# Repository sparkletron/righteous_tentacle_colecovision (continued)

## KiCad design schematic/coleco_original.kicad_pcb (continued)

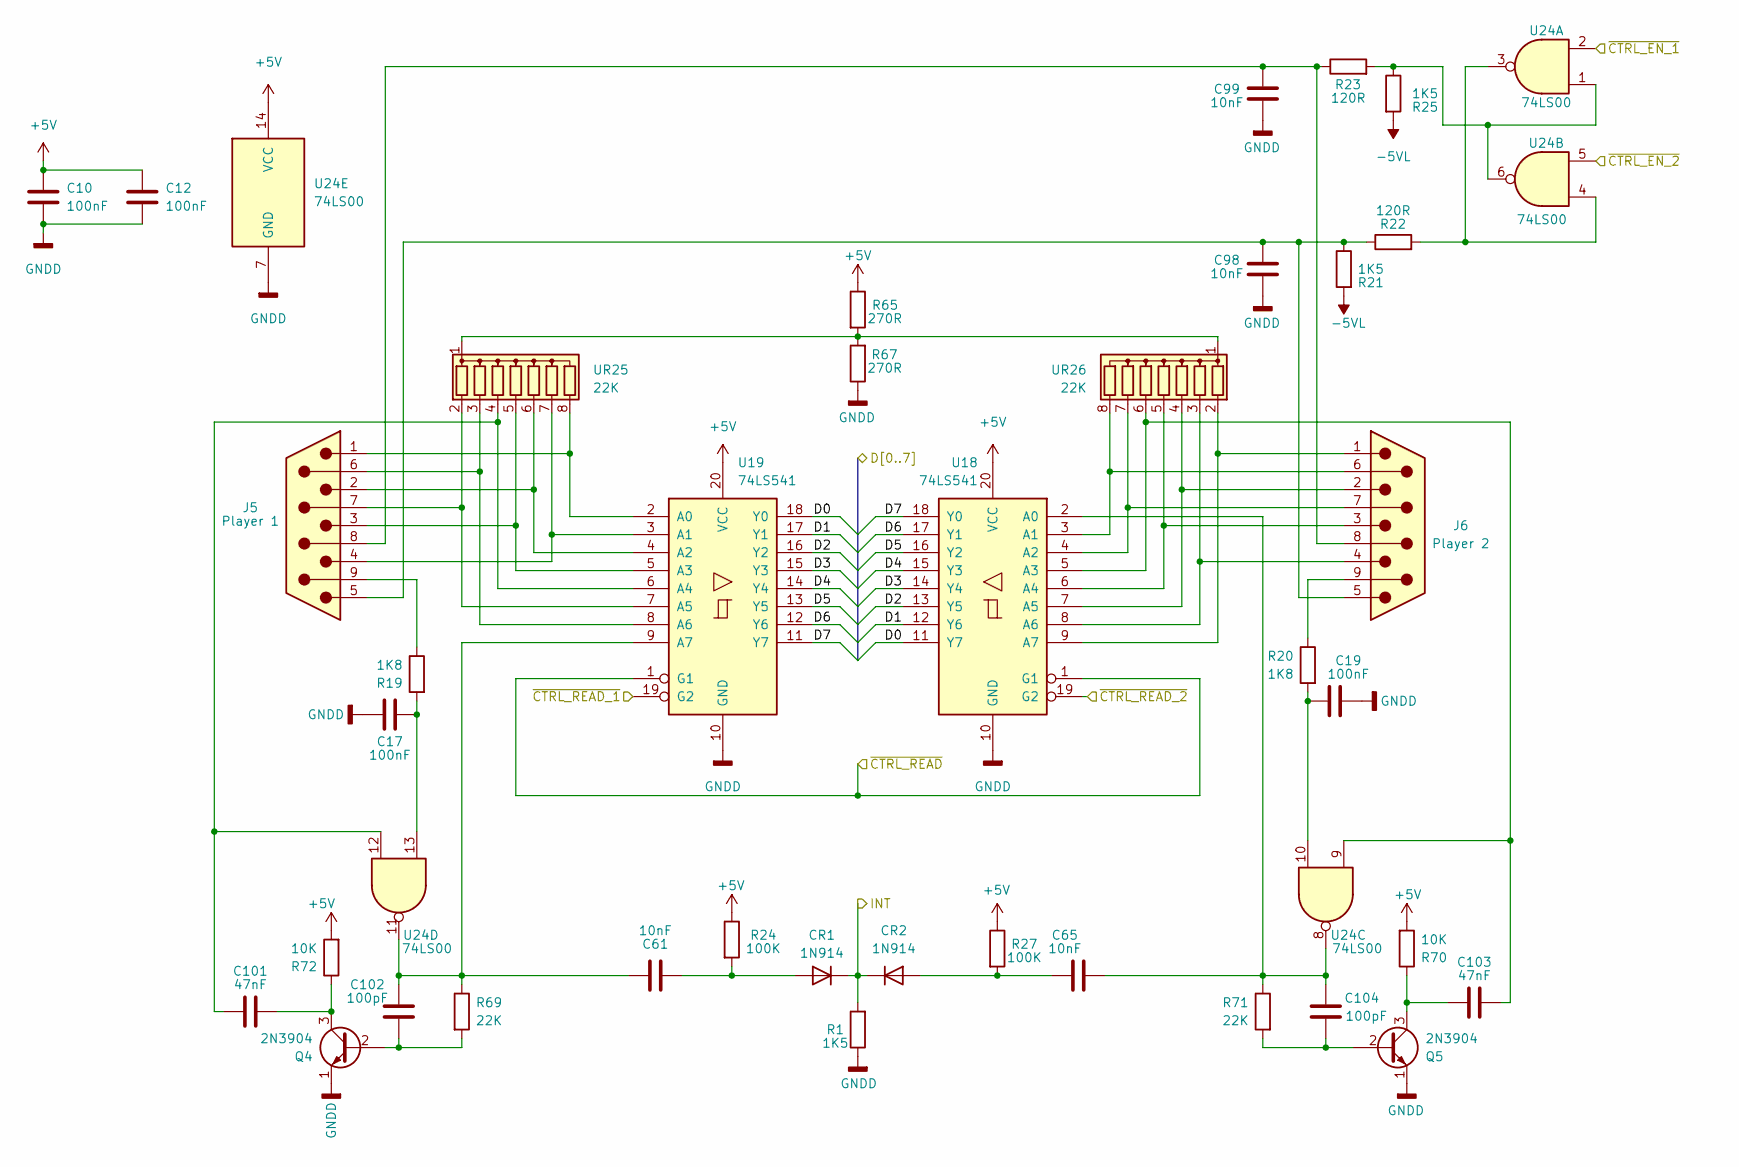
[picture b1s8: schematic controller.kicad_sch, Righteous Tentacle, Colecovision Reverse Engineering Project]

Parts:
C10, C12, C17, C19: 100nF; C_Disc_D7.0mm_W2.5mm_P5.00mm
C61, C65, C98, C99: 10nF; C_Disc_D7.0mm_W2.5mm_P5.00mm
C101, C103: 47nF; C_Disc_D7.0mm_W2.5mm_P5.00mm
C102, C104: 100pF; C_Disc_D7.0mm_W2.5mm_P5.00mm
CR1, CR2: 1N914; D_DO-35_SOD27_P10.16mm_Horizontal
J5: Player 1; DSUB-9_Male_Horizontal_P2.77x2.84mm_EdgePinOffset7.70mm_Hou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
J6: Player 2; DSUB-9_Male_Horizontal_P2.77x2.84mm_EdgePinOffset7.70mm_Hou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
Q4, Q5: 2N3904; TO-92_Wide
R1, R21, R25: 1K5; R_Axial_DIN0207_L6.3mm_D2.5mm_P10.16mm_Horizontal
R19, R20: 1K8; R_Axial_DIN0207_L6.3mm_D2.5mm_P10.16mm_Horizontal
R22, R23: 120R; R_Axial_DIN0207_L6.3mm_D2.5mm_P10.16mm_Horizontal
R24, R27: 100K; R_Axial_DIN0207_L6.3mm_D2.5mm_P10.16mm_Horizontal
R65, R67: 270R; R_Axial_DIN0207_L6.3mm_D2.5mm_P10.16mm_Horizontal
R69, R71: 22K; R_Axial_DIN0207_L6.3mm_D2.5mm_P10.16mm_Horizontal
R70, R72: 10K; R_Axial_DIN0207_L6.3mm_D2.5mm_P10.16mm_Horizontal
U18, U19: 74LS541; DIP-20_W7.62mm_LongPads
U24: 74LS00; DIP-14_W7.62mm_LongPads
UR25, UR26: 22K; R_Array_SIP8

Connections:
+5V: C10.1, C12.1, R24.1, R27.1, R65.1, R70.2, R72.2, U18.20 (VCC), U19.20 (VCC), U24.14 (VCC); also elsewhere on the board
-5VL: R21.2, R25.2; also elsewhere on the board
/clock_reset_misc_logic/INT: CR1.1 (K), CR2.1 (K), R1.2; also elsewhere on the board
/clock_reset_misc_logic/~CTRL_READ_2: U18.19 (G2); also elsewhere on the board
/controller/~CTRL_EN_1: U24.2; also elsewhere on the board
/controller/~CTRL_EN_2: U24.5; also elsewhere on the board
/controller/~CTRL_READ: U18.1 (G1), U19.1 (G1); also elsewhere on the board
/cpu/A1: U19.19 (G2); also elsewhere on the board
/cpu/D0: U18.11 (Y7), U19.18 (Y0); also elsewhere on the board
/cpu/D1: U18.12 (Y6), U19.17 (Y1); also elsewhere on the board
/cpu/D2: U18.13 (Y5), U19.16 (Y2); also elsewhere on the board
/cpu/D3: U18.14 (Y4), U19.15 (Y3); also elsewhere on the board
/cpu/D4: U18.15 (Y3), U19.14 (Y4); also elsewhere on the board
/cpu/D5: U18.16 (Y2), U19.13 (Y5); also elsewhere on the board
/cpu/D6: U18.17 (Y1), U19.12 (Y6); also elsewhere on the board
/cpu/D7: U18.18 (Y0), U19.11 (Y7); also elsewhere on the board
GNDD: C10.2, C12.2, C17.1, C19.1, C98.1, C99.2, Q4.1 (E), Q5.1 (E), R1.1, R67.1, U18.10 (GND), U19.10 (GND), U24.7 (GND); also elsewhere on the board
unnamed: C17.2, R19.2, U24.13
unnamed: C19.2, R20.2, U24.10
unnamed: C61.1, CR1.2 (A), R24.2
unnamed: C65.1, CR2.2 (A), R27.2
unnamed: C98.2, J5.5, J6.5, R21.1, R22.1
unnamed: C99.1, J5.8, J6.8, R23.1
unnamed: C101.1, Q4.3 (C), R72.1
unnamed: C101.2, U19.6 (A4), U24.12, UR25.4 (R3)
unnamed: C102.1, Q4.2 (B), R69.2
unnamed: C61.2, C102.2, R69.1, U19.9 (A7), U24.11
unnamed: C103.1, Q5.3 (C), R70.1
unnamed: C103.2, U18.5 (A3), U24.9, UR26.6 (R5)
unnamed: C104.1, Q5.2 (B), R71.2
unnamed: C65.2, C104.2, R71.1, U18.2 (A0), U24.8
unnamed: J5.1, U19.2 (A0), UR25.8 (R7)
unnamed: J5.2, U19.4 (A2), UR25.6 (R5)
unnamed: J5.3, U19.5 (A3), UR25.5 (R4)
unnamed: J5.4, U19.3 (A1), UR25.7 (R6)
unnamed: J5.6, U19.8 (A6), UR25.3 (R2)
unnamed: J5.7, U19.7 (A5), UR25.2 (R1)
unnamed: J5.9, R19.1
unnamed: J6.1, U18.9 (A7), UR26.2 (R1)
unnamed: J6.2, U18.7 (A5), UR26.4 (R3)
unnamed: J6.3, U18.6 (A4), UR26.5 (R4)
unnamed: J6.4, U18.8 (A6), UR26.3 (R2)
unnamed: J6.6, U18.3 (A1), UR26.8 (R7)
unnamed: J6.7, U18.4 (A2), UR26.7 (R6)
unnamed: J6.9, R20.1
unnamed: R22.2, U24.3, U24.4
unnamed: R23.2, R25.1, U24.1, U24.6
unnamed: R65.2, R67.2, UR25.1 (common), UR26.1 (common)

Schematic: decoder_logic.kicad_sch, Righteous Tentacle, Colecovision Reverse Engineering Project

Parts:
C2: 100nF; C_Disc_D7.0mm_W2.5mm_P5.00mm
U5, U6: 74LS138; DIP-16_W7.62mm_LongPads

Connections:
+5V: C2.1, U5.16 (VCC); also elsewhere on the board
+5VD: U6.16 (VCC); also elsewhere on the board
/clock_reset_misc_logic/RFSH: U5.5 (E2); also elsewhere on the board
/clock_reset_misc_logic/~AUD_DECODE_2: U6.5 (E2); also elsewhere on the board
/controller/~CTRL_EN_1: U6.11 (O4); also elsewhere on the board
/controller/~CTRL_EN_2: U6.15 (O0); also elsewhere on the board
/controller/~CTRL_READ: U6.7 (O7); also elsewhere on the board
/cpu/A5: U6.2 (A1); also elsewhere on the board
/cpu/A6: U6.3 (A2); also elsewhere on the board
/cpu/A7: U6.6 (E3); also elsewhere on the board
/cpu/A13: U5.1 (A0); also elsewhere on the board
/cpu/A14: U5.2 (A1); also elsewhere on the board
/cpu/A15: U5.3 (A2); also elsewhere on the board
/cpu/~IORQ: U6.4 (E1); also elsewhere on the board
/cpu/~MREQ: U5.4 (E1); also elsewhere on the board
/cpu/~WR: U6.1 (A0); also elsewhere on the board
/decoder_logic/AUX_DECODE_1: U5.6 (E3); also elsewhere on the board
/decoder_logic/~CSR: U6.12 (O3); also elsewhere on the board
/decoder_logic/~CSW: U6.13 (O2); also elsewhere on the board
/decoder_logic/~CS_h2000: U5.14 (O1); also elsewhere on the board
/decoder_logic/~CS_h4000: U5.13 (O2); also elsewhere on the board
/decoder_logic/~CS_h8000: U5.11 (O4); also elsewhere on the board
/decoder_logic/~CS_hA000: U5.10 (O5); also elsewhere on the board
/decoder_logic/~CS_hC000: U5.9 (O6); also elsewhere on the board
/decoder_logic/~CS_hE000: U5.7 (O7); also elsewhere on the board
/decoder_logic/~RAM_CS: U5.12 (O3); also elsewhere on the board
/decoder_logic/~ROM_ENABLE: U5.15 (O0); also elsewhere on the board
/decoder_logic/~SND_ENABLE: U6.9 (O6); also elsewhere on the board
GNDD: C2.2, U5.8 (GND), U6.8 (GND); also elsewhere on the board

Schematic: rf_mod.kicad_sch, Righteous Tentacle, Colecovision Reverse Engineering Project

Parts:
C57, C78: 10nF; C_Disc_D7.0mm_W2.5mm_P5.00mm
C60, C69: 47nF; C_Disc_D7.0mm_W2.5mm_P5.00mm
C62, C63: 470pF; C_Disc_D7.0mm_W2.5mm_P5.00mm
C64: 120pF; C_Disc_D7.0mm_W2.5mm_P5.00mm
C66, C67, C88, C100: 100nF; C_Disc_D7.0mm_W2.5mm_P5.00mm
C68: 10uF; CP_Radial_D8.0mm_P5.00mm
C87: 10uF; CP_Radial_D5.0mm_P2.50mm
H8, H9, H10, H11, H12: MountingHole_Pad; RF_MOUNT
H13: MountingHole_Pad; MountingHole_4.3mm_M4_ISO14580_Pad
H14, H15: MountingHole_Pad; MountingHole_2.2mm_M2_DIN965_Pad
J4A1: Conn_01x08; PinHeader_1x08_P2.54mm_Vertical
L7, L8: 120uH; L_Axial_L11.0mm_D4.5mm_P7.62mm_Vertical_Fastron_MECC
L9, L15: 42uH; L_Axial_L11.0mm_D4.5mm_P7.62mm_Vertical_Fastron_MECC
L10: 10uH; L_Axial_L11.0mm_D4.5mm_P7.62mm_Vertical_Fastron_MECC
Q3, Q6: 2N3906; TO-92_Wide
R18, R55, R76: 1K8; R_Axial_DIN0207_L6.3mm_D2.5mm_P10.16mm_Horizontal
R40, R41, R42: 390R; R_Axial_DIN0207_L6.3mm_D2.5mm_P10.16mm_Horizontal
R43, R49: 10K; R_Axial_DIN0207_L6.3mm_D2.5mm_P10.16mm_Horizontal
R48: 470K; R_Axial_DIN0207_L6.3mm_D2.5mm_P10.16mm_Horizontal
R79: 1K5_OPT; R_Axial_DIN0207_L6.3mm_D2.5mm_P10.16mm_Horizontal
U23: 4066; DIP-14_W7.62mm_LongPads

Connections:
+12VL: Q3.1 (E), R76.2, R79.1, U23.14 (VDD); also elsewhere on the board
/clock_reset_misc_logic/SND_CLK: L15.2; also elsewhere on the board
/io_ports/EXT_SOUND: C88.1; also elsewhere on the board
/io_ports/EXT_VIDEO: U23.9; also elsewhere on the board
/io_ports/SND_OUT: R18.2; also elsewhere on the board
/rf_mod/B-Y: L8.2; also elsewhere on the board
/rf_mod/R-Y: L7.2; also elsewhere on the board
/rf_mod/Y: L9.1; also elsewhere on the board
/rf_mod/sub_rf_mod/2: C100.2, J4A1.2; also elsewhere on the board
/rf_mod/sub_rf_mod/3: C66.1, J4A1.3, U23.4; also elsewhere on the board
/rf_mod/sub_rf_mod/6: J4A1.6, R55.1, U23.8; also elsewhere on the board
/rf_mod/sub_rf_mod/7: C67.2, J4A1.7, U23.1; also elsewhere on the board
/rf_mod/sub_rf_mod/8: C78.1, J4A1.8; also elsewhere on the board
GNDD: C57.2, C60.2, C62.2, C63.2, C64.2, C87.2, H8.1, H9.1, H10.1, H11.1, H12.1, H13.1, H14.1, H15.1, J4A1.1, Q6.3 (C), R40.2, R41.2, R42.2, R43.1, R49.2, U23.7 (VSS); also elsewhere on the board
unnamed: C62.1, C66.2, L7.1, R40.1
unnamed: C63.1, C67.1, L8.1, R41.1
unnamed: C64.1, L9.2, Q6.2 (B), R42.1
unnamed: C68.1, C69.2, R55.2, R79.2, U23.11
unnamed: C68.2, Q6.1 (E), R76.1
unnamed: C78.2, L15.1
unnamed: C88.2, C100.1, R18.1
unnamed: Q3.3 (C), R49.1, U23.5, U23.12, U23.13
VDDA: C60.1, L10.2; also elsewhere on the board

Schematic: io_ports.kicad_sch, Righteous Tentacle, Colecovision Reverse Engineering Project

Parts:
C9: 100nF; C_Disc_D7.0mm_W2.5mm_P5.00mm
J1: Cartridge Port; 55308412_coleco
J2: Expansion Port; Colecovision_Expansion
R16: 3K3; R_Axial_DIN0207_L6.3mm_D2.5mm_P10.16mm_Horizontal
R26: 470R; R_Axial_DIN0207_L6.3mm_D2.5mm_P10.16mm_Horizontal

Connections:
+5V: C9.1, J1.30, J2.58, J2.59, R16.1; also elsewhere on the board
+12VL: J2.57; also elsewhere on the board
-5VL: J2.60; also elsewhere on the board
/clock_reset_misc_logic/AUX_DECODE_2: J2.30; also elsewhere on the board
/clock_reset_misc_logic/EXP_RESET: J2.34; also elsewhere on the board
/clock_reset_misc_logic/INT: J2.10; also elsewhere on the board
/clock_reset_misc_logic/RESET: J2.36; also elsewhere on the board
/clock_reset_misc_logic/SND_CLK: J2.35; also elsewhere on the board
/clock_reset_misc_logic/~CLK: J2.45, R26.2; also elsewhere on the board
/clock_reset_misc_logic/~INT: J2.51; also elsewhere on the board
/clock_reset_misc_logic/~M1: J2.15; also elsewhere on the board
/clock_reset_misc_logic/~RESET: J2.13; also elsewhere on the board
/clock_reset_misc_logic/~RFSH: J2.49; also elsewhere on the board
/clock_reset_misc_logic/~WAIT: J2.50; also elsewhere on the board
/cpu/A0: J1.7, J2.47; also elsewhere on the board
/cpu/A1: J1.9, J2.18; also elsewhere on the board
/cpu/A2: J1.11, J2.20; also elsewhere on the board
/cpu/A3: J1.15, J2.44; also elsewhere on the board
/cpu/A4: J1.17, J2.21; also elsewhere on the board
/cpu/A5: J1.21, J2.23; also elsewhere on the board
/cpu/A6: J1.23, J2.24; also elsewhere on the board
/cpu/A7: J1.25, J2.25; also elsewhere on the board
/cpu/A8: J1.28, J2.26; also elsewhere on the board
/cpu/A9: J1.26, J2.27; also elsewhere on the board
/cpu/A10: J1.16, J2.28; also elsewhere on the board
/cpu/A11: J1.14, J2.37; also elsewhere on the board
/cpu/A12: J1.24, J2.38; also elsewhere on the board
/cpu/A13: J1.19, J2.22; also elsewhere on the board
/cpu/A14: J1.20, J2.4; also elsewhere on the board
/cpu/A15: J2.43; also elsewhere on the board
/cpu/D0: J1.5, J2.14; also elsewhere on the board
/cpu/D1: J1.3, J2.12; also elsewhere on the board
/cpu/D2: J1.1, J2.46; also elsewhere on the board
/cpu/D3: J1.4, J2.3; also elsewhere on the board
/cpu/D4: J1.6, J2.19; also elsewhere on the board
/cpu/D5: J1.8, J2.48; also elsewhere on the board
/cpu/D6: J1.10, J2.17; also elsewhere on the board
/cpu/D7: J1.12, J2.16; also elsewhere on the board
/cpu/~BUSAK: J2.52; also elsewhere on the board
/cpu/~BUSRQ: J2.11; also elsewhere on the board
/cpu/~HALT: J2.7; also elsewhere on the board
/cpu/~IORQ: J2.55; also elsewhere on the board
/cpu/~MREQ: J2.54; also elsewhere on the board
/cpu/~NMI: J2.9; also elsewhere on the board
/cpu/~RD: J2.53; also elsewhere on the board
/cpu/~WR: J2.8; also elsewhere on the board
/decoder_logic/AUX_DECODE_1: J2.29, R16.2; also elsewhere on the board
/decoder_logic/~CS_h2000: J2.6; also elsewhere on the board
/decoder_logic/~CS_h4000: J2.5; also elsewhere on the board
/decoder_logic/~CS_h8000: J1.18; also elsewhere on the board
/decoder_logic/~CS_hA000: J1.22; also elsewhere on the board
/decoder_logic/~CS_hC000: J1.2; also elsewhere on the board
/decoder_logic/~CS_hE000: J1.27; also elsewhere on the board
/io_ports/EXT_SOUND: J2.31; also elsewhere on the board
/io_ports/EXT_VIDEO: J2.33; also elsewhere on the board
/io_ports/SND_OUT: J2.56; also elsewhere on the board
/io_ports/~VDP_RESET: J2.39; also elsewhere on the board
GND: J1.13; also elsewhere on the board
GNDD: C9.2, J1.29, J2.1, J2.2; also elsewhere on the board
unnamed: J2.40, R26.1

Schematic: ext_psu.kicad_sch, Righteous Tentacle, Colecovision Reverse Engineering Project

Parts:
J3: Conn_01x04; Molex_KK-396_A-41791-0004_1x04_P3.96mm_Vertical
J4: DIN-5_180degree

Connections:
unnamed: J3.1, J4.1, J4.2
unnamed: J3.2, J4.4
unnamed: J3.3, J4.5
unnamed: J3.4, J4.3

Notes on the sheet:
MEAN WELL 28.5 Watt PSU: GP25A13A-R1B GP25B13A-R1B This page shows how to wire the internal power cable between the board header and the external PSU jack.

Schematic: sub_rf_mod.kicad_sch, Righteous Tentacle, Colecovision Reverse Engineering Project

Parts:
H16, H17: MountingHole_Pad; MountingHole_2.2mm_M2_DIN965_Pad
J4B1: Conn_01x08; PinSocket_1x08_P2.54mm_Vertical
RF_C1: 1nF; C_Disc_D7.0mm_W2.5mm_P5.00mm
RF_C2, RF_C3, RF_C8: 10nF; C_Disc_D7.0mm_W2.5mm_P5.00mm
RF_C4, RF_C5, RF_C7: 47pF; C_Disc_D7.0mm_W2.5mm_P5.00mm
RF_C6, RF_C9: 82pF; C_Disc_D7.0mm_W2.5mm_P5.00mm
RF_C10: 10pF; C_Disc_D7.0mm_W2.5mm_P5.00mm
RF_C11: 270pF; C_Disc_D7.0mm_W2.5mm_P5.00mm
RF_C12: 20pF; C_Disc_D7.0mm_W2.5mm_P5.00mm
RF_C13: 10uF; CP_Radial_D5.0mm_P2.00mm
RF_D1: 1N753; D_DO-35_SOD27_P10.16mm_Horizontal
RF_D2: BB329A; D_DO-35_SOD27_P10.16mm_Horizontal
RF_J1: RF_OUT; RCJ041_copy
RF_JP1: Jumper_2_Bridged; R_Axial_DIN0207_L6.3mm_D2.5mm_P15.24mm_Horizontal
RF_L1, RF_L2: 1.4uH; L_Radial_D7.5mm_P5.00mm_Fastron_07P
RF_L3: 1.5uH; L_Radial_D7.5mm_P5.00mm_Fastron_07P
RF_R1, RF_R10: 39K; R_Axial_DIN0207_L6.3mm_D2.5mm_P7.62mm_Horizontal
RF_R2, RF_R3, RF_R4: 1K; R_Axial_DIN0207_L6.3mm_D2.5mm_P7.62mm_Horizontal
RF_R5, RF_R6: 240R; R_Axial_DIN0207_L6.3mm_D2.5mm_P7.62mm_Horizontal
RF_R7: 47R; R_Axial_DIN0207_L6.3mm_D2.5mm_P7.62mm_Horizontal
RF_R8: 82R; R_Axial_DIN0207_L6.3mm_D2.5mm_P7.62mm_Horizontal
RF_R9: 8K2; R_Axial_DIN0207_L6.3mm_D2.5mm_P7.62mm_Horizontal
RF_R11: 4K7; R_Axial_DIN0207_L6.3mm_D2.5mm_P7.62mm_Horizontal
RF_R12: 15K; R_Axial_DIN0207_L6.3mm_D2.5mm_P7.62mm_Horizontal
RF_SW1: SW_SPDT; 1101M2S3ABE2
RF_U1: LM1889; DIP-18_W7.62mm_LongPads
RF_VL1: Sumida_73279
S5: rf_board_rev; rf_board_revision

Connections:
/rf_mod/sub_rf_mod/2: J4B1.2, RF_C2.2, RF_D2.2 (A), RF_R1.2, RF_R10.2; also elsewhere on the board
/rf_mod/sub_rf_mod/3: J4B1.3, RF_U1.2 (R-Y); also elsewhere on the board
/rf_mod/sub_rf_mod/6: J4B1.6, RF_U1.13 (CHROMA_SUBCAR); also elsewhere on the board
/rf_mod/sub_rf_mod/7: J4B1.7, RF_U1.4 (B-Y); also elsewhere on the board
/rf_mod/sub_rf_mod/8: J4B1.8, RF_C4.2, RF_R2.2; also elsewhere on the board
GNDD: H16.1, H17.1, J4B1.1, RF_C1.2, RF_C2.1, RF_C8.2, RF_C9.2, RF_C11.2, RF_C13.2, RF_J1.S, RF_R3.1, RF_R4.1, RF_R7.2, RF_U1.5 (GND), RF_VL1.S; also elsewhere on the board
unnamed: RF_C3.1, RF_U1.1 (CHROMA_LEAD)
unnamed: RF_C3.2, RF_C4.1, RF_R3.2
unnamed: RF_C5.1, RF_R2.1, RF_U1.18 (CHROMA_LAG)
unnamed: RF_C6.1, RF_L3.1, RF_R5.2, RF_SW1.2 (B), RF_U1.7 (CHB_TANK2)
unnamed: RF_C7.1, RF_R12.1
unnamed: RF_C10.1, RF_L2.2
unnamed: RF_C9.1, RF_C10.2, RF_L1.1, RF_R7.1
unnamed: RF_C11.1, RF_J1.T, RF_L1.2
unnamed: RF_C12.1, RF_SW1.1 (A)
unnamed: RF_C6.2, RF_C12.2, RF_L3.2, RF_R6.1, RF_U1.6 (CHB_TANK1)
unnamed: RF_D2.1 (K), RF_R12.2, RF_U1.15 (SOUND_TANK), RF_VL1.1
unnamed: RF_L2.1, RF_R8.1, RF_U1.10 (CHB_OUTPUT)

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
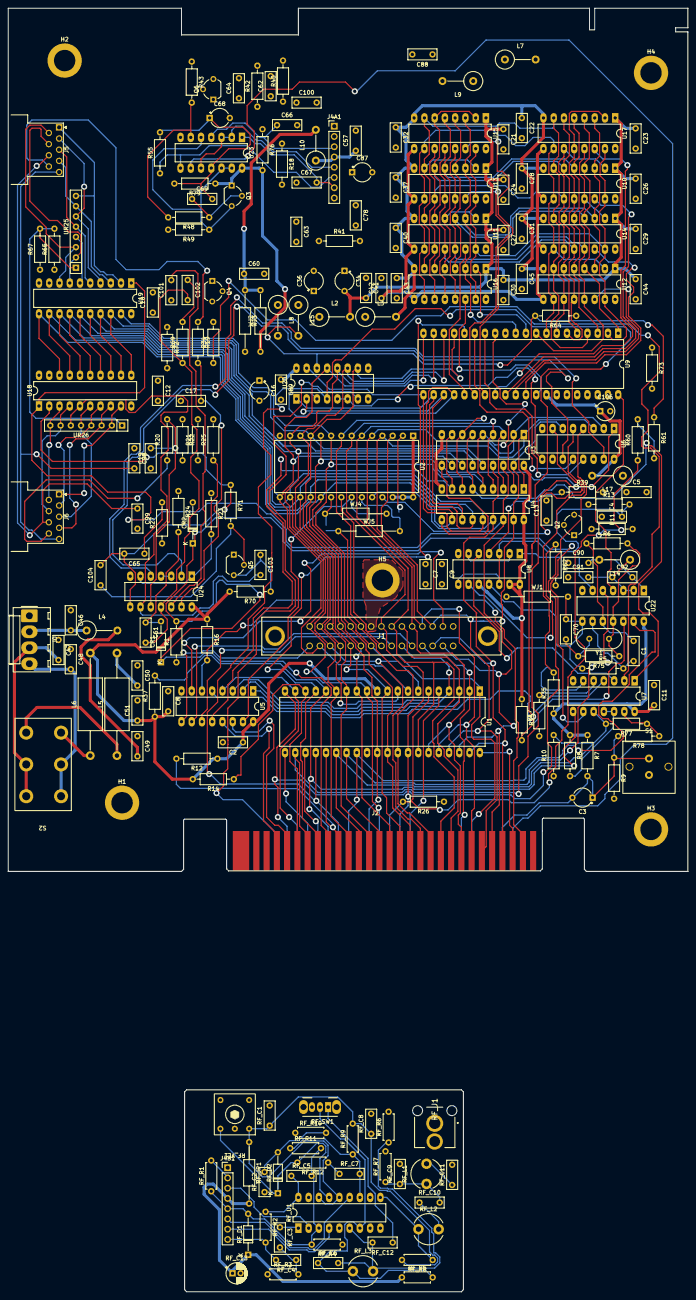
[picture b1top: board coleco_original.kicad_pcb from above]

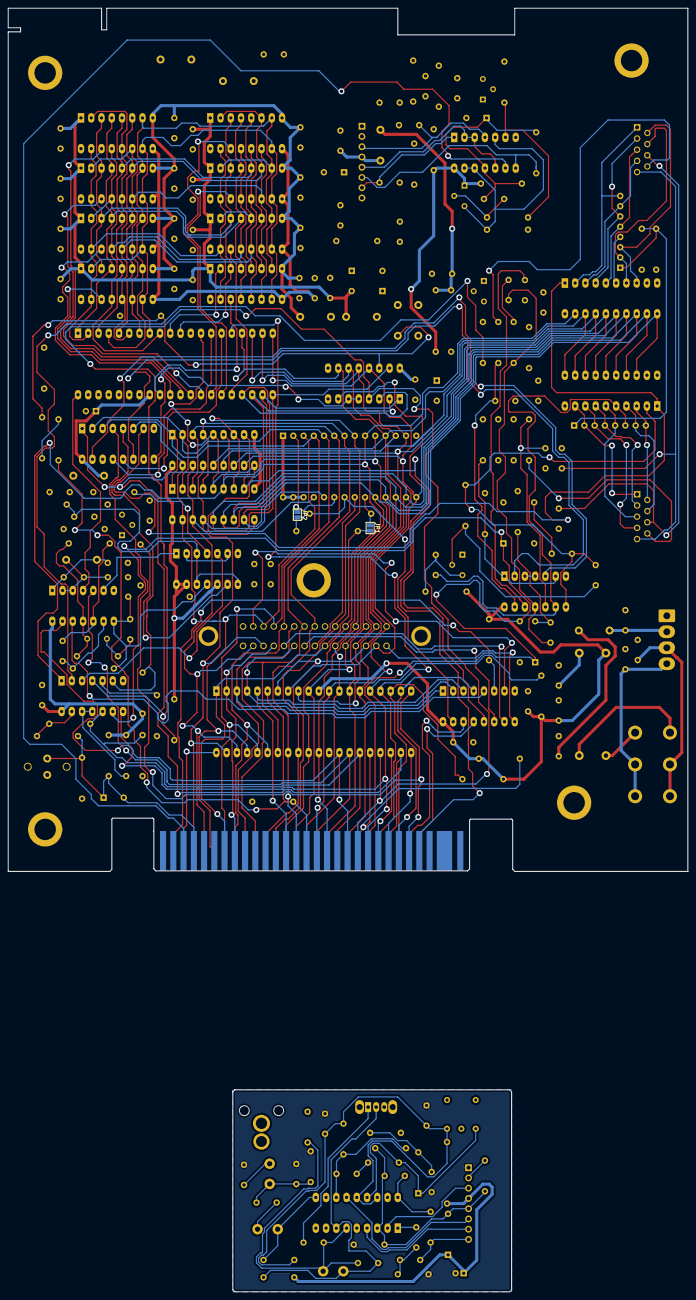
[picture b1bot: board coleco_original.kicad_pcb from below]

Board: 2 copper layers, 168.4 x 213.9 mm, 220 parts (2 on the bottom side), 183 nets.

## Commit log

2022-11-03 init commit
2022-11-03 fix ascii
2022-11-03 spelling
2022-11-08 reorganized repo
2022-12-28 changed up library, fixed color of blocks and organization. Added new 2114 RAM
2022-12-28 added hi-res pics of stripped PCB
2022-12-28 first day of pcb trace, working pin by of the z80 cpu. Last pin completed: 7
2022-12-29 revised schematic into sheets for easier design. Looks much better.
2022-12-29 worked on the z80 trace up to and including pin 15.
2022-12-30 changed all vintage library names to better represent future ideas. Removed parts not needed... for now. Updated schmematic symbols.
2022-12-31 Up to pin 29 on z80 done. Address 0 to 10 left. Only tracing to its end point for the most part. Each chip gets traced chip to chip in this manned
2022-12-31 completed Z80 trace of PCB. off to a good start.
2023-01-02 added rf modulation schematic, added dram to vdp. Fixed +5vc to +5v
2023-01-02 added u5 decoder lines, need to rename for chip selects that they actually are in future.
2023-01-02 added u6 decoder lines, renamed a few lines to make sense to there destination.
2023-01-03 completed sound block, finished cart io port, and finished decoder.
2023-01-03 fixed some more line names, added a expansion port io pin.
2023-01-03 power supply added, controller circuit added. Controller is a very odd duck to say the least. Seems they wanted to have plenty of current, maybe due to the steering wheel attachement?
2023-01-03 started work on clock_reset_misc circuits. inverter u7 done, u8 added and starting work around U22.
2023-01-04 first version of clock-reset circuits. Its a bit complicated and will need some revisions.
2023-01-04 altered and did some cleanup of the way the wires were run. Finished expansion port routes to rf modulator. Added ext_psu for future external power supply design (will be an off the shelf psu block).
2023-01-04 added rf mod section, this is very rough. Has mistakes for sure.
2023-01-04 RF modulator completed, rough draft complete. Next step is to clean-up all pages.
2023-01-08 Cleanup clock-reset-invert schematic. Checked against wiki.console5.com/wiki/Colecovision. Had a inverter backwards (after cleanup it was obvious since its a standard circuit). Everything else checks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
2023-01-08 cleanup on the controller schematic. Checked against wiki.console5.com/wiki/Colecovision. Found a mistake with INT line thanks to the wiki. R21/R22 is reversed between the schematics. Aka R21 is plac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
2023-01-08 cleaup of rf circuits. much better flow vs the original. Comparing to the wiki.console5.com/wiki/Colecovision shows many differences. Not sure I agree with it at all. Going to use the ADAM schematic 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
2023-01-09 cleanup of power supply, and another pass at the RF circuit. Both look much better. The RF circuit just looks wrong though. Will need to check it over.
2023-01-09 cleaned up RF circuit again, and used ChildOfCv schematic as a ref. Fixed a few mistakes. I didn't know his even existed. Its a very nice project. I didn't know it existed till I was googling some so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
2023-01-09 added my refs so people will know where the 2nd phase of checks came from. its really helped the effort, the goal is to reverse the board from the original, and use online sources to check, and then 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
2023-01-10 all lines renamed, based most of the names from the coleco adam schematic. CS cart lines are my own, and the rest are from the wiki schematic for the controller... those will need to be checked.
2023-01-10 adjusted size of the sheets. added pcb version to the rev field. F.0... the 0 is for future fixes on my end. RF PCB is E.0.
2023-01-15 cleanup, and started associating components
2023-01-16 added new libs for rest of the parts. some still need updating for correct parts, but for now they work. PCB import complete.
2023-01-16 created edge cut outline for coleco pcb. updated expansion connector edge cut to be the correct size (using a 0.8 mm cutting end in my mill).
2023-01-16 place a few components for an alignment check. changed edge cut back to 0.1. added new edge.cuts.mill layer for pcb mill edge cuts
2023-02-06 first draft of board with components added, no traces
2023-02-07 added a quick version of the RF board. Not checked at all.
2023-02-12 fixed RF board placement, not perfect, but needs to align to new component sizes
2023-02-13 RF on main board components setup correctly.
2023-02-14 did a small amount of pcb work, also finished component directions for the main board. RF pcb is still a mess and needs a second pass.
2023-02-20 added controller traces and some around it.
2023-02-20 added addr decode and 4066 circuit
2023-02-20 added video memory connections
2023-02-22 added traces to parts of the clock gen/reset ic's
2023-02-28 fixed a bug on the +5v line, added +5NF (no filter) net list names. Added traces to the ram, and inverter, and select ics.
2023-03-02 added memory, eprom and sound lines. some video as well. fixed the cap size for polar. its a bit weird since they use 5 mm pin and 5mm body and bend out the leads.
2023-03-04 updated license and added info to readme
2023-03-04 working on eeprom, cart port, cpu
2023-03-04 most of the semi-conductors are done.
2023-03-05 first rough draft completed. very rough, needs alot of cleanup. all rats connected besides board to board.
2023-03-05 compress images to fit on github
2023-03-05 changed files again since PNG was the issue
2023-03-11 started cleanup of traces, working on the bottom layer first.
2023-03-11 working on top layer, improved the routing and respacing traces.
2023-03-13 added a new jack with matching pin names. started fixing drc errors. start working on power trace sizes.
2023-03-14 added new models, fixed the drc errors. changed power width.
2023-03-14 updated schematic with new layout
2023-03-14 change connector to female
2023-03-14 added power cable pinout, cleanup finished on main page of schematic, now fits US letter page.
2023-03-17 added pads for switch and RF shield, RF shield still needs adjustment
2023-03-17 fixed mount spacing, added labels, and added new version of reset switch.
2023-03-17 imporved power rails, added 3D models (primitives at this point till others can be made).
2023-03-19 cleanup controller schematic
2023-03-19 cleanup main schematic to remove crossing lines
2023-03-19 added pdf schematic, cleanup pdf files, added 3D image, updated readme
2023-03-20 some cleanup on the rf main circuit. tested out and reverted 10 mil to 12 mil spacing. Fails on cart connector.
2023-03-23 fixed cart for 12 mil isolation routing. Now minimum trace isolation is 12 mil. Trace width min is 12 mil. This is easier to build.
2023-03-23 tweak rf schematic
2023-03-24 trace cleanup, and RF mod schematic cleanup
2023-03-24 cleanup grounds
2023-03-24 more trace cleanup
2023-03-25 adjusted connector and switch to remove ignored clearance errors
2023-03-25 adjust gnd iso width to better connect all grounds in video ram (20 down to 12mil)
2023-03-25 added pics to repo, removed main_board project
2023-03-25 update 3d image and pcbs for export
2023-03-28 changed via size to 22 mill for better fitment
2023-03-29 cleanup and readjust of traces, copied to gerber export projects.
2023-03-30 enlarged mount holes to match coleco, adjusted placement of two. adjusted traces for new holes.
2023-03-30 updated switch for better fitment, check npth vs pth. exported updated pdf version of schematic
2023-04-03 fixed two resistors that were the wrong value wrong, 270. correct 120.
2023-04-03 changed the board from the original so the control ports can be soldered from the bottom. standard dsub 9 bin connectors don't work on non-plated hole designs. All other parts can be soldered top and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
2023-04-03 adjusted controller ports again, now they are totally soldered from the bottom for front and BACK rows. added some no fill zones and some general cleanup as well.
2023-04-03 updated video input of the rf section, easier to read.
2023-04-03 added mounting holes, future proof the video section for jumper selection of voltages between 4516/4116 chips
2023-04-04 adjusted rf mod porition for better flow
2023-04-06 moved crystal line to bottom for easier soldering.
2023-04-07 changed crystal a bit more to make double sided non-plated through hole designs easier. This time top traces rerouted to avoid shorts from the crystal body.
2023-04-08 updated schematic PDF, updated 3D image. Updated all gerber files, and small adjustments to the pcb to cleanup traces.
2023-04-08 updated docs/datasheets with all of the ICS. updated readme to help people better navigate the repo.
2023-04-08 github links suck
2023-04-08 fixed indent on file list
2023-04-09 fixed cap value, adjusted rf lines on main board to make npt hole assembly easier
2023-04-09 fixed value of resistors on RF board, fixed placement of resistors on RF board
2023-04-09 fixed readme indents
2023-04-10 adjusting RF layout, seems to have issues with the previous layout with noise
2023-04-11 fixed footprint lead size
2023-04-12 pdf added, and changes to data bus to resolve shorting issues between cart and rom
2023-04-13 changed switch to one that is a better match for the old (larger)
2023-04-14 update routing of rf board to fix loop over pin
2023-05-01 changed a few traces, and updated a few parts. cleanup to make building easier so resistors don't have vias under them for npth builds
2023-05-01 changed clock line so it wouldn't keep the resistor out of place on npth builds
2023-05-01 cleanup for release of version 1
2023-05-05 added first set of digital signal captures
2023-05-05 made sure all schematic parts are up to date
2023-05-08 reorg of the repo to make schematic dir easier to nav
2023-05-10 updated switch to fix isolation size. fixed some traces to prevent shorts when being build at home with mills or etching methods.
2023-05-13 updated gerbers and main/rf exports
2023-05-21 fixed pad size for switch
2023-05-22 fixed 5v via so it doesn't hold up the resistor
2023-05-23 fixed some t-tech edge cut for the main board.
2023-05-23 adjusted 5 volt trace on 7405
2023-05-23 fixed the switch for the sub-rf board to match the original coleco for chan 3/4 selection
2023-05-25 first commit of verison 1.0.0, missing documents for signals and 3D enclosure.
2023-05-26 added analog signals
2023-05-26 whoops, spelling for the win
2023-05-26 added info to pic names
2023-05-26 added vdp pics
2023-05-26 added F to version number in readme. this indicates the board revision from coleco the current version is based on.
2023-05-26 ntsc note
2023-05-26 updated readme defines for folders
2023-05-26 added intro
2023-05-26 added image
2023-05-26 update pdf with spelling fix
2023-05-26 update to kicad 7.0, ipt stuff added
2023-05-28 added new power supply info
2023-05-28 added 3D printed case parts... in progress.
2023-05-28 altered mount lower right point by moving 20 right and 20 down (mills)
2023-05-28 added new kicad 3d model of pcb... coleco_original3.iam is the best. odd bug that the switch comes out clear
2023-05-28 updated kicad pcb hole to be only 10 mils to the right. That seemed to work perfect, and the new printed shell fits the board decently enough.
2023-06-19 3D printed part adjust, fix cart position.
2023-06-19 added F to revision, update date
2023-06-20 added switch 3d models and updated readme
2023-06-20 added images of case, updated readme.
2024-03-25 fixed for github
2024-06-05 updated schematic so IORQn is a input on io_ports sheet
2024-06-05 update pdf
2024-10-10 added zip'd gerbers for pcb house, these are NOT tested.
2024-11-08 update gerbers in zip files to remove edge.cuts.mill. This caused issues with JLCPCB per user Tekman on Atari Age
2024-11-08 testing update to readme, remove kicad lock file
2024-11-08 add some info since download links are not instant
2024-11-08 remove kicad lock file
2024-11-08 remove backups
2024-11-08 added gitignore rules for backup kicad files. lock files are now ignored
2024-12-02 remove solder mask from edge connector (thanks to Tekman@AtariAge for pointing this out), update gerbers and version
